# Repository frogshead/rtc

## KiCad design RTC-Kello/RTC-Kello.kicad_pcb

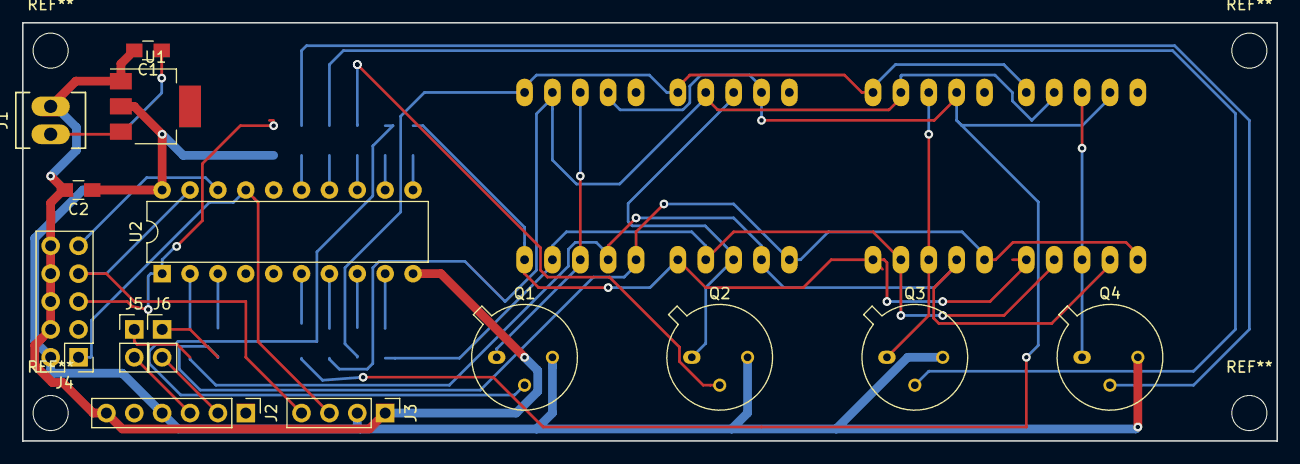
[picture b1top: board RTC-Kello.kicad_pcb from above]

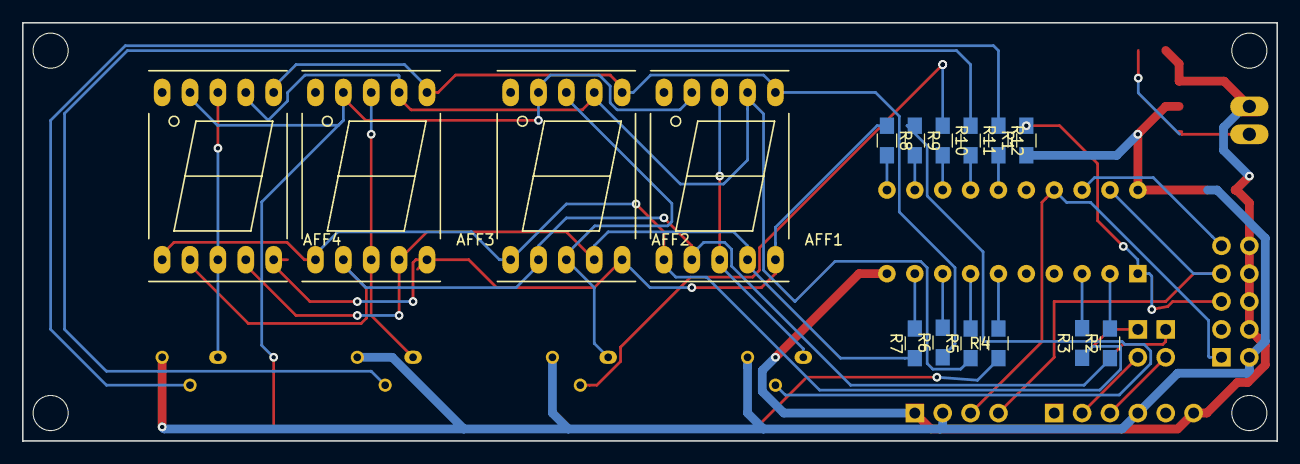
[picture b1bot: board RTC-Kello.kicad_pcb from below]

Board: 2 copper layers, 114.3 x 38.1 mm, 30 parts (16 on the bottom side), 35 nets.

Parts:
AFF1, AFF2, AFF3, AFF4: LTS-6960HR; 7SegmentLED_LTS6760_LTS6780
C1: 100n; C_0805_HandSoldering
C2: 10u; C_0805_HandSoldering
J1: Screw_Terminal_1x02; Socket_MOLEX-KK-RM2-54mm_Lock_2pin_straight
J2: CONN_01X06; Pin_Header_Straight_1x06_Pitch2.54mm
J3: CONN_01X04; Pin_Header_Straight_1x04_Pitch2.54mm
J4: CONN_02X05; Pin_Header_Straight_2x05_Pitch2.54mm
J5, J6: CONN_01X02; Pin_Header_Straight_1x02_Pitch2.54mm
Q1, Q2, Q3, Q4: 2N2219; TO-39-3
R1: 10k; R_0805_HandSoldering
R2, R3, R4, R5, R6, R7, R8: R; R_0805_HandSoldering
R9, R10, R11, R12: 1k; R_0805_HandSoldering
U1: LD1117S33CTR; SOT-223
U2: ATTINY2313-20PU; DIP-20_W7.62mm

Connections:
+3V3: C2.1, J2.4, J3.2, J4.2, Q1.3, Q2.3, Q3.3, Q4.3, R1.1, U1.2, U2.20
/Disp_1: R9.2, U2.12
/Disp_2: R10.2, U2.13
/Disp_3: R11.2, U2.14
/Disp_4: R12.2, U2.15
/MISO: J4.9, U2.18
/MOSI: J3.3, J4.1, U2.17
/RST: J4.5, R1.2, U2.1
/SCK: J3.4, J4.7, U2.19
/a: AFF1.7, AFF2.7, AFF3.7, AFF4.7, J5.1, R2.1
/b: AFF1.6, AFF2.6, AFF3.6, AFF4.6, J6.1, R3.1
/c: AFF1.4, AFF2.4, AFF3.4, AFF4.4, R4.1
/d: AFF1.2, AFF2.2, AFF3.2, AFF4.2, R5.1
/e: AFF1.1, AFF2.1, AFF3.1, AFF4.1, R6.1
/f: AFF1.9, AFF2.9, AFF3.9, AFF4.9, R7.1
/g: AFF1.10, AFF2.10, AFF3.10, AFF4.10, R8.1
GND: C1.2, C2.2, J1.2, J2.6, J3.1, J4.4, J4.6, J4.8, J4.10, U1.1, U2.10
unnamed: AFF1.3, AFF1.8, Q1.1
unnamed: AFF2.3, AFF2.8, Q2.1
unnamed: AFF3.3, AFF3.8, Q3.1
unnamed: AFF4.3, AFF4.8, Q4.1
unnamed: C1.1, J1.1, U1.3
unnamed: J2.2, J6.2
unnamed: J2.3, J5.2
unnamed: Q1.2, R9.1
unnamed: Q2.2, R10.1
unnamed: Q3.2, R11.1
unnamed: Q4.2, R12.1
unnamed: R2.2, U2.2
unnamed: R3.2, U2.3
unnamed: R4.2, U2.6
unnamed: R5.2, U2.7
unnamed: R6.2, U2.8
unnamed: R7.2, U2.9
unnamed: R8.2, U2.11

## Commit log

2017-08-13 First version where tracks routed on pcb
2017-08-14 PCB send to OSH Park
2017-09-30 DS3231 i2c communication working
2017-09-30 Add Makefile
2017-10-05 Fixes for ds3231 lib to work with i2c lib
2017-10-23 Automatically change time between normal and summer time
2017-10-24 Clean up and update
2017-12-17 backup to github :)
